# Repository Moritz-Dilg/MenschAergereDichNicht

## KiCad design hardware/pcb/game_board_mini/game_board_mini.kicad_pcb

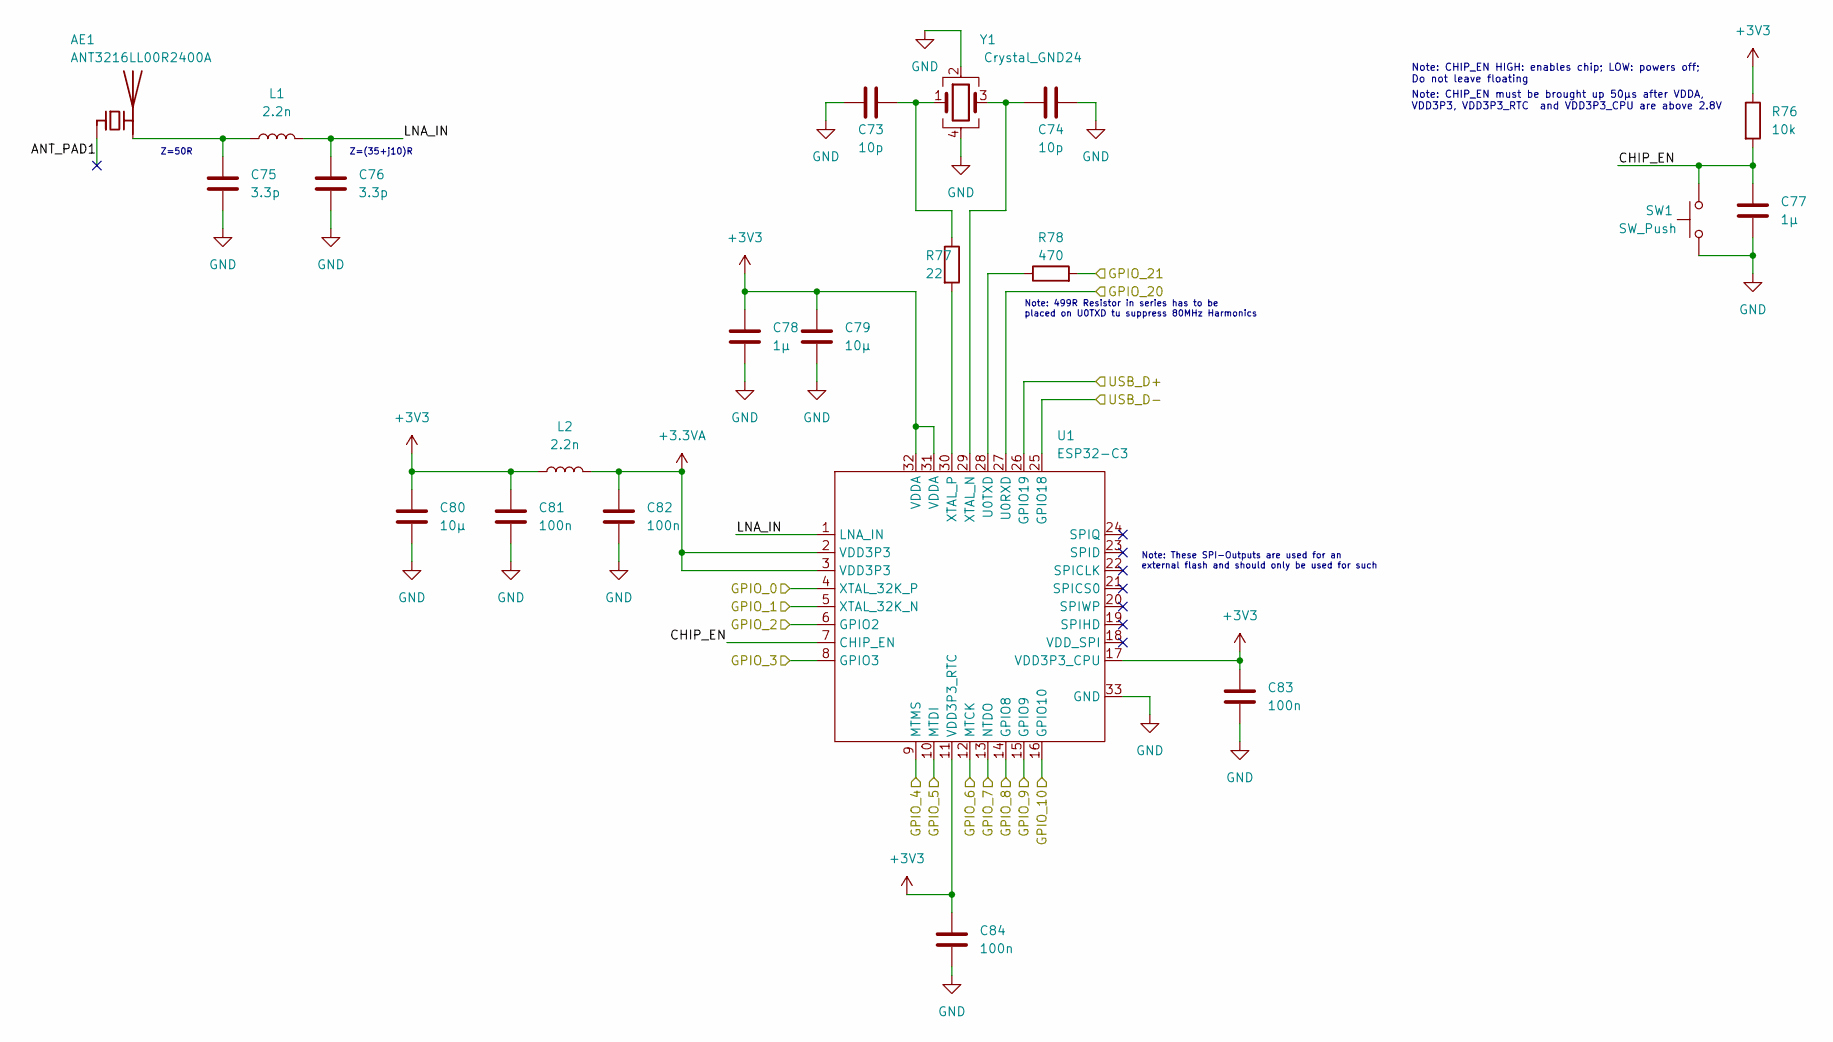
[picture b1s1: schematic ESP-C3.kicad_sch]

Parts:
AE1: ANT3216LL00R2400A
C73, C74: 10p; C_0603_1608Metric
C75, C76: 3.3p; C_0603_1608Metric
C77, C78: 1µ; C_0603_1608Metric
C79, C80: 10µ; C_0603_1608Metric
C81, C82, C83, C84: 100n; C_0603_1608Metric
L1, L2: 2.2n; L_0603_1608Metric
R76: 10k; R_0603_1608Metric
R77: 22; R_0603_1608Metric
R78: 470; R_0603_1608Metric
SW1: SW_Push
U1: ESP32-C3; QFN-32-1EP_5x5mm_P0.5mm_EP3.3x3.3mm_ThermalVias
Y1: Crystal_GND24; Crystal_SMD_3225-4Pin_3.2x2.5mm

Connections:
+3.3VA: C82.1, L2.2, U1.2 (VDD3P3), U1.3 (VDD3P3)
+3V3: C78.1, C79.1, C80.1, C81.1, C83.1, C84.1, L2.1, R76.1, U1.11 (VDD3P3_RTC), U1.17 (VDD3P3_CPU), U1.31 (VDDA), U1.32 (VDDA); also elsewhere on the board
/BL: U1.27 (U0RXD); also elsewhere on the board
/Button_1: U1.8 (GPIO3); also elsewhere on the board
/Button_2: U1.9 (MTMS); also elsewhere on the board
/Button_3: U1.10 (MTDI); also elsewhere on the board
/CS: U1.12 (MTCK); also elsewhere on the board
/Connectors/EN_TFT: R78.2
/DC: U1.13 (NTDO); also elsewhere on the board
/Din_BASE: U1.4 (XTAL_32K_P); also elsewhere on the board
/Din_FIELD: U1.5 (XTAL_32K_N); also elsewhere on the board
/Din_GOAL: U1.6 (GPIO2); also elsewhere on the board
/ESP-C3/ANT_PAD1: AE1.1 (FEED)
/ESP-C3/CHIP_EN: C77.1, R76.2, SW1.2, U1.7 (CHIP_EN)
/ESP-C3/LNA_IN: C76.1, L1.2, U1.1 (LNA_IN)
/ESP-C3/USB_D+: U1.26 (GPIO19); also elsewhere on the board
/ESP-C3/USB_D-: U1.25 (GPIO18); also elsewhere on the board
/MOSI: U1.16 (GPIO10); also elsewhere on the board
/RST: U1.14 (GPIO8); also elsewhere on the board
/SCK: U1.15 (GPIO9); also elsewhere on the board
GND: C73.1, C74.2, C75.2, C76.2, C77.2, C78.2, C79.2, C80.2, C81.2, C82.2, C83.2, C84.2, SW1.1, U1.33 (GND), Y1.2, Y1.4; also elsewhere on the board
unnamed: AE1.2 (PCB_Trace), C75.1, L1.1
unnamed: C73.2, R77.1, Y1.1
unnamed: C74.1, U1.29 (XTAL_N), Y1.3
unnamed: R77.2, U1.30 (XTAL_P)
unnamed: R78.1, U1.28 (U0TXD)

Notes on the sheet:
Note: 499R Resistor in series has to be placed on U0TXD tu suppress 80MHz Harmonics
Note: CHIP_EN must be brought up 50µs after VDDA, VDD3P3, VDD3P3_RTC and VDD3P3_CPU are above 2.8V
Note: CHIP_EN HIGH: enables chip; LOW: powers off; Do not leave floating
Z=50R
Note: These SPI-Outputs are used for an external flash and should only be used for such
Z=(35+j10)R

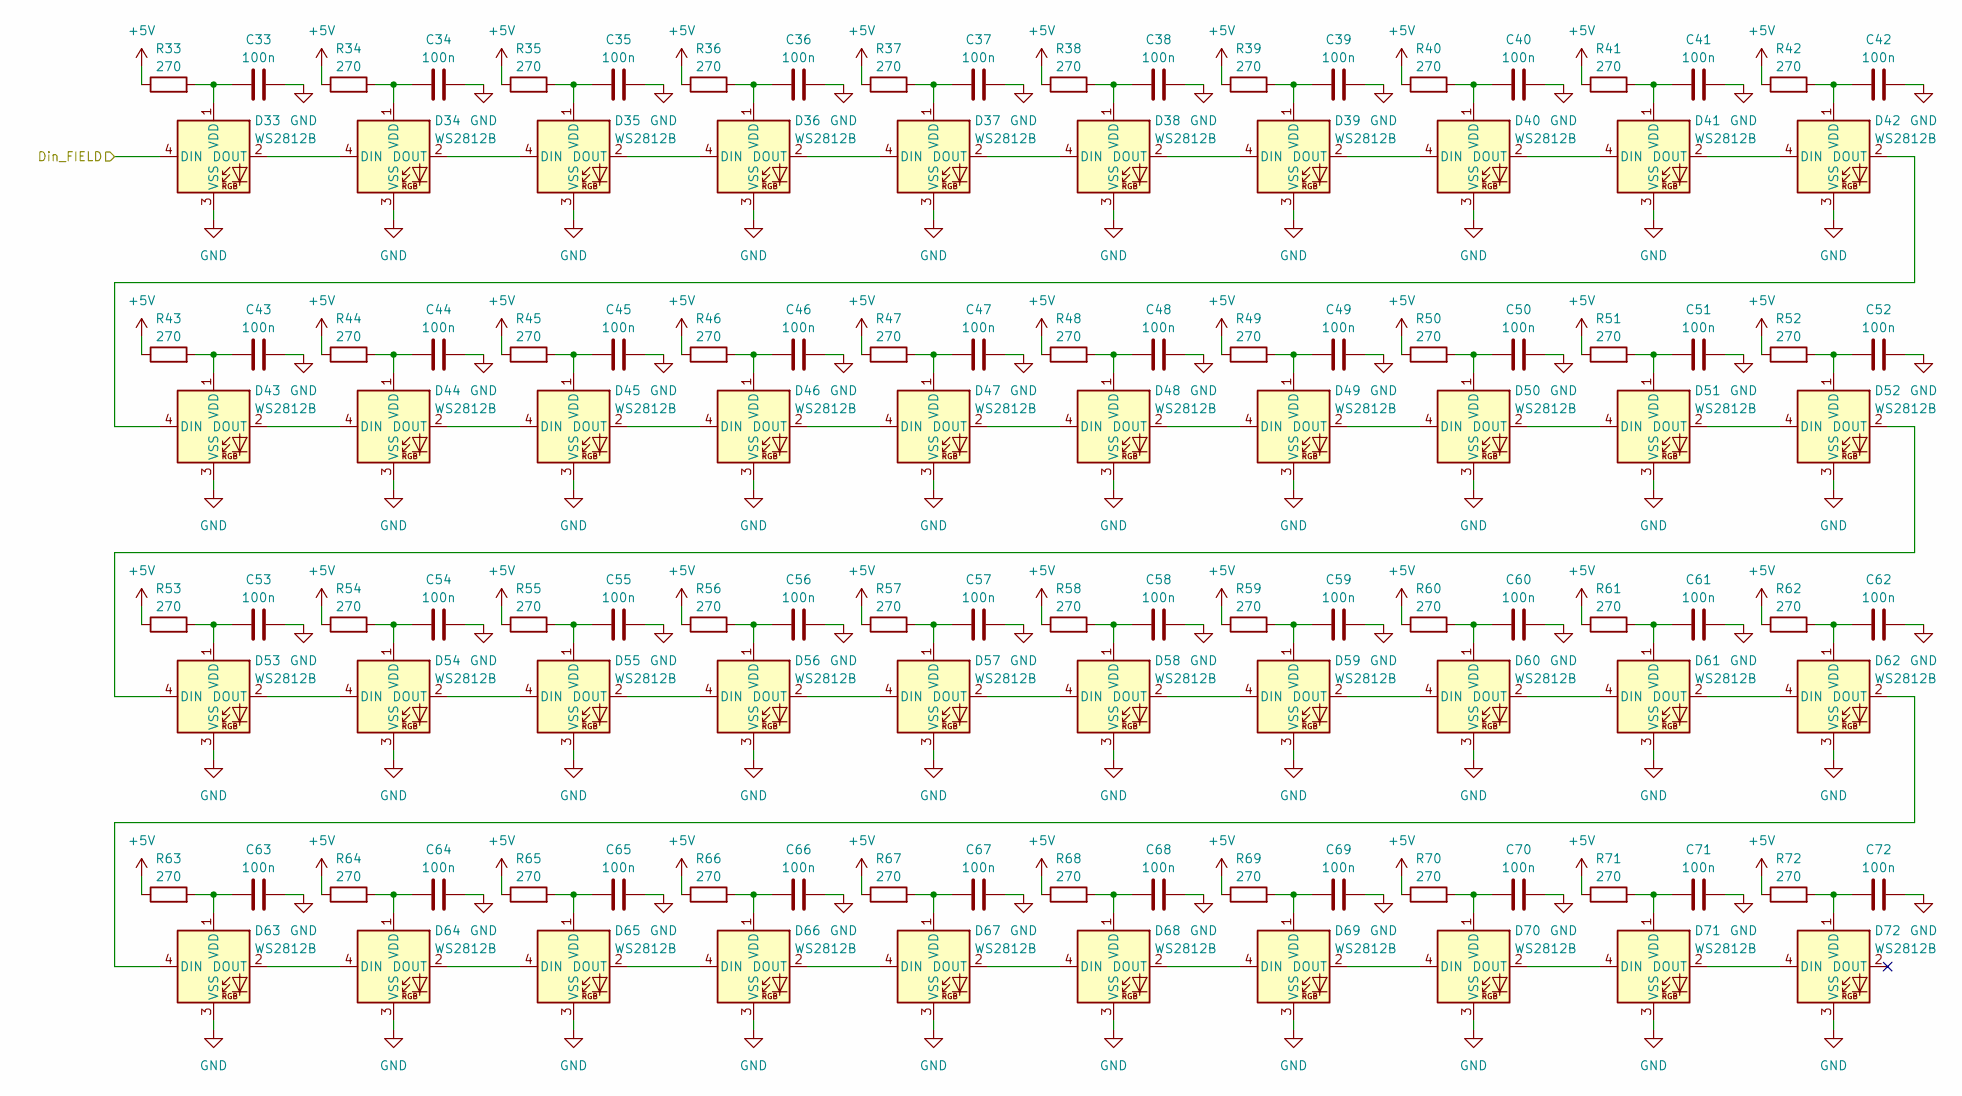
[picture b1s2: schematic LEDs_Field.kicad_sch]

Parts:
C33, C34, C35, C36, C37, C38, C39, C40, C41, C42, C43, C44, C45, C46, C47, C48, C49, C50, C51, C52, C53, C54, C55, C56, C57, C58, C59, C60, C61, C62, C63, C64, C65, C66, C67, C68, C69, C70, C71, C72: 100n; C_0603_1608Metric
D33, D34, D35, D36, D37, D38, D39, D40, D41, D42, D43, D44, D45, D46, D47, D48, D49, D50, D51, D52, D53, D54, D55, D56, D57, D58, D59, D60, D61, D62, D63, D64, D65, D66, D67, D68, D69, D70, D71, D72: WS2812B; LED_WS2812B-2020_PLCC4_2.0x2.0mm
R33, R34, R35, R36, R37, R38, R39, R40, R41, R42, R43, R44, R45, R46, R47, R48, R49, R50, R51, R52, R53, R54, R55, R56, R57, R58, R59, R60, R61, R62, R63, R64, R65, R66, R67, R68, R69, R70, R71, R72: 270; R_0603_1608Metric

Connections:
+5V: R33.1, R34.1, R35.1, R36.1, R37.1, R38.1, R39.1, R40.1, R41.1, R42.1, R43.1, R44.1, R45.1, R46.1, R47.1, R48.1, R49.1, R50.1, R51.1, R52.1, R53.1, R54.1, R55.1, R56.1, R57.1, R58.1, R59.1, R60.1, R61.1, R62.1, R63.1, R64.1, R65.1, R66.1, R67.1, R68.1, R69.1, R70.1, R71.1, R72.1; also elsewhere on the board
/Din_FIELD: D33.4 (DIN); also elsewhere on the board
GND: C33.2, C34.2, C35.2, C36.2, C37.2, C38.2, C39.2, C40.2, C41.2, C42.2, C43.2, C44.2, C45.2, C46.2, C47.2, C48.2, C49.2, C50.2, C51.2, C52.2, C53.2, C54.2, C55.2, C56.2, C57.2, C58.2, C59.2, C60.2, C61.2, C62.2, C63.2, C64.2, C65.2, C66.2, C67.2, C68.2, C69.2, C70.2, C71.2, C72.2, D33.3 (VSS), D34.3 (VSS), D35.3 (VSS), D36.3 (VSS), D37.3 (VSS), D38.3 (VSS), D39.3 (VSS), D40.3 (VSS), D41.3 (VSS), D42.3 (VSS), D43.3 (VSS), D44.3 (VSS), D45.3 (VSS), D46.3 (VSS), D47.3 (VSS), D48.3 (VSS), D49.3 (VSS), D50.3 (VSS), D51.3 (VSS), D52.3 (VSS), D53.3 (VSS), D54.3 (VSS), D55.3 (VSS), D56.3 (VSS), D57.3 (VSS), D58.3 (VSS), D59.3 (VSS), D60.3 (VSS), D61.3 (VSS), D62.3 (VSS), D63.3 (VSS), D64.3 (VSS), D65.3 (VSS), D66.3 (VSS), D67.3 (VSS), D68.3 (VSS), D69.3 (VSS), D70.3 (VSS), D71.3 (VSS), D72.3 (VSS); also elsewhere on the board
unnamed: C33.1, D33.1 (VDD), R33.2
unnamed: C34.1, D34.1 (VDD), R34.2
unnamed: C35.1, D35.1 (VDD), R35.2
unnamed: C36.1, D36.1 (VDD), R36.2
unnamed: C37.1, D37.1 (VDD), R37.2
unnamed: C38.1, D38.1 (VDD), R38.2
unnamed: C39.1, D39.1 (VDD), R39.2
unnamed: C40.1, D40.1 (VDD), R40.2
unnamed: C41.1, D41.1 (VDD), R41.2
unnamed: C42.1, D42.1 (VDD), R42.2
unnamed: C43.1, D43.1 (VDD), R43.2
unnamed: C44.1, D44.1 (VDD), R44.2
unnamed: C45.1, D45.1 (VDD), R45.2
unnamed: C46.1, D46.1 (VDD), R46.2
unnamed: C47.1, D47.1 (VDD), R47.2
unnamed: C48.1, D48.1 (VDD), R48.2
unnamed: C49.1, D49.1 (VDD), R49.2
unnamed: C50.1, D50.1 (VDD), R50.2
unnamed: C51.1, D51.1 (VDD), R51.2
unnamed: C52.1, D52.1 (VDD), R52.2
unnamed: C53.1, D53.1 (VDD), R53.2
unnamed: C54.1, D54.1 (VDD), R54.2
unnamed: C55.1, D55.1 (VDD), R55.2
unnamed: C56.1, D56.1 (VDD), R56.2
unnamed: C57.1, D57.1 (VDD), R57.2
unnamed: C58.1, D58.1 (VDD), R58.2
unnamed: C59.1, D59.1 (VDD), R59.2
unnamed: C60.1, D60.1 (VDD), R60.2
unnamed: C61.1, D61.1 (VDD), R61.2
unnamed: C62.1, D62.1 (VDD), R62.2
unnamed: C63.1, D63.1 (VDD), R63.2
unnamed: C64.1, D64.1 (VDD), R64.2
unnamed: C65.1, D65.1 (VDD), R65.2
unnamed: C66.1, D66.1 (VDD), R66.2
unnamed: C67.1, D67.1 (VDD), R67.2
unnamed: C68.1, D68.1 (VDD), R68.2
unnamed: C69.1, D69.1 (VDD), R69.2
unnamed: C70.1, D70.1 (VDD), R70.2
unnamed: C71.1, D71.1 (VDD), R71.2
unnamed: C72.1, D72.1 (VDD), R72.2
unnamed: D33.2 (DOUT), D34.4 (DIN)
unnamed: D34.2 (DOUT), D35.4 (DIN)
unnamed: D35.2 (DOUT), D36.4 (DIN)
unnamed: D36.2 (DOUT), D37.4 (DIN)
unnamed: D37.2 (DOUT), D38.4 (DIN)
unnamed: D38.2 (DOUT), D39.4 (DIN)
unnamed: D39.2 (DOUT), D40.4 (DIN)
unnamed: D40.2 (DOUT), D41.4 (DIN)
unnamed: D41.2 (DOUT), D42.4 (DIN)
unnamed: D42.2 (DOUT), D43.4 (DIN)
unnamed: D43.2 (DOUT), D44.4 (DIN)
unnamed: D44.2 (DOUT), D45.4 (DIN)
unnamed: D45.2 (DOUT), D46.4 (DIN)
unnamed: D46.2 (DOUT), D47.4 (DIN)
unnamed: D47.2 (DOUT), D48.4 (DIN)
unnamed: D48.2 (DOUT), D49.4 (DIN)
unnamed: D49.2 (DOUT), D50.4 (DIN)
unnamed: D50.2 (DOUT), D51.4 (DIN)
unnamed: D51.2 (DOUT), D52.4 (DIN)
unnamed: D52.2 (DOUT), D53.4 (DIN)
unnamed: D53.2 (DOUT), D54.4 (DIN)
unnamed: D54.2 (DOUT), D55.4 (DIN)
unnamed: D55.2 (DOUT), D56.4 (DIN)
unnamed: D56.2 (DOUT), D57.4 (DIN)
unnamed: D57.2 (DOUT), D58.4 (DIN)
unnamed: D58.2 (DOUT), D59.4 (DIN)
unnamed: D59.2 (DOUT), D60.4 (DIN)
unnamed: D60.2 (DOUT), D61.4 (DIN)
unnamed: D61.2 (DOUT), D62.4 (DIN)
unnamed: D62.2 (DOUT), D63.4 (DIN)
unnamed: D63.2 (DOUT), D64.4 (DIN)
unnamed: D64.2 (DOUT), D65.4 (DIN)
unnamed: D65.2 (DOUT), D66.4 (DIN)
unnamed: D66.2 (DOUT), D67.4 (DIN)
unnamed: D67.2 (DOUT), D68.4 (DIN)
unnamed: D68.2 (DOUT), D69.4 (DIN)
unnamed: D69.2 (DOUT), D70.4 (DIN)
unnamed: D70.2 (DOUT), D71.4 (DIN)
unnamed: D71.2 (DOUT), D72.4 (DIN)

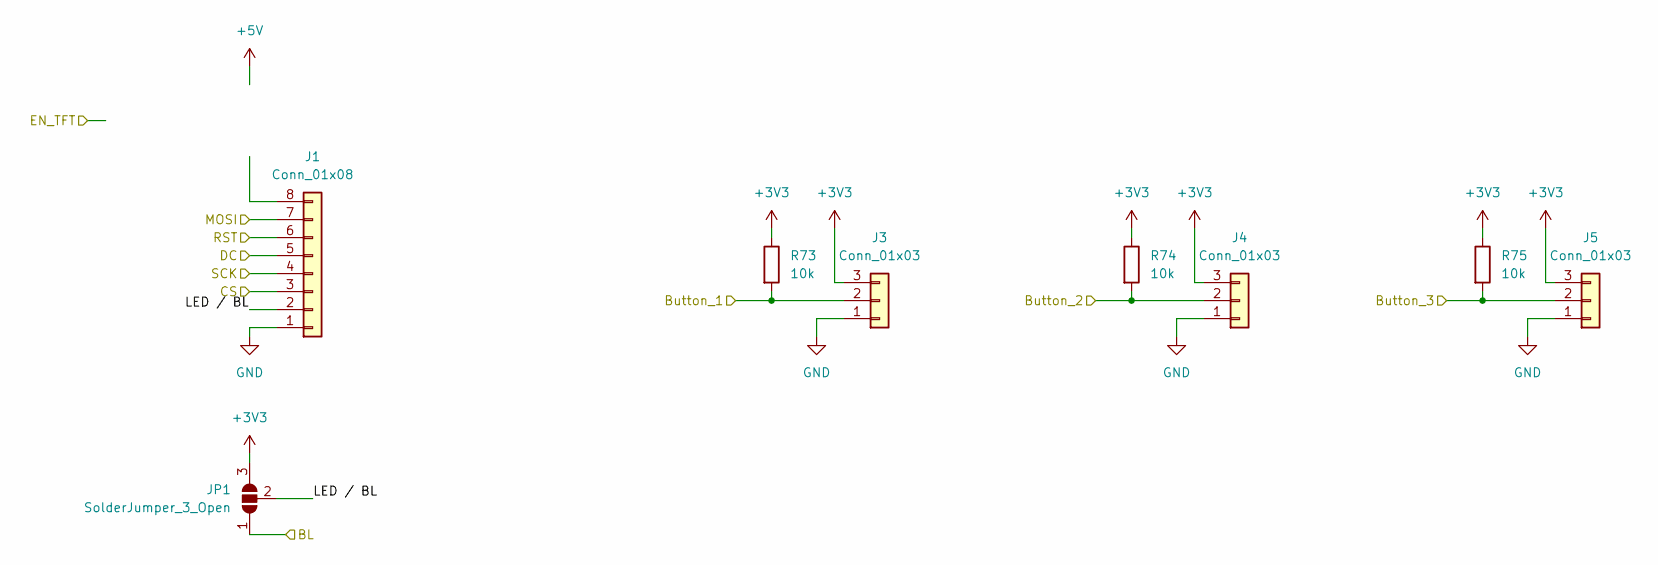
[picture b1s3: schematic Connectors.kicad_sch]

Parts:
J1: Conn_01x08; JST_PH_B8B-PH-K_1x08_P2.00mm_Vertical
J3, J4, J5: Conn_01x03; JST_PH_B3B-PH-K_1x03_P2.00mm_Vertical
JP1: SolderJumper_3_Open; SolderJumper-3_P1.3mm_Open_Pad1.0x1.5mm
R73, R74, R75: 10k; R_0805_2012Metric

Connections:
+3V3: J3.3, J4.3, J5.3, JP1.3 (B), R73.1, R74.1, R75.1; also elsewhere on the board
/BL: JP1.1 (A); also elsewhere on the board
/Button_1: J3.2, R73.2; also elsewhere on the board
/Button_2: J4.2, R74.2; also elsewhere on the board
/Button_3: J5.2, R75.2; also elsewhere on the board
/CS: J1.3; also elsewhere on the board
/Connectors/LED / BL: J1.2, JP1.2 (C)
/DC: J1.5; also elsewhere on the board
/MOSI: J1.7; also elsewhere on the board
/RST: J1.6; also elsewhere on the board
/SCK: J1.4; also elsewhere on the board
GND: J1.1, J3.1, J4.1, J5.1; also elsewhere on the board

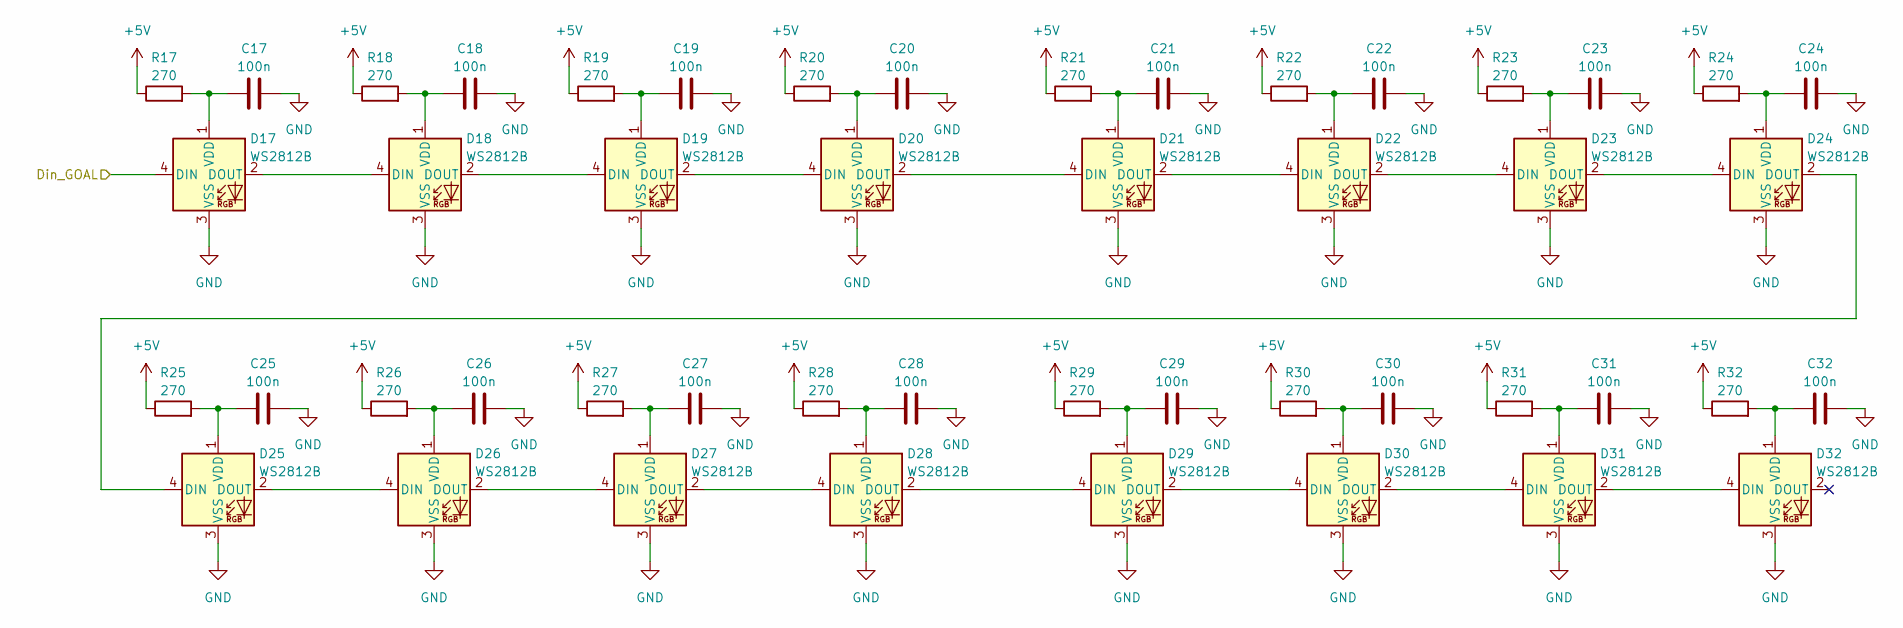
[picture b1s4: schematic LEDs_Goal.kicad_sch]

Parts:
C17, C18, C19, C20, C21, C22, C23, C24, C25, C26, C27, C28, C29, C30, C31, C32: 100n; C_0603_1608Metric
D17, D18, D19, D20, D21, D22, D23, D24, D25, D26, D27, D28, D29, D30, D31, D32: WS2812B; LED_WS2812B-2020_PLCC4_2.0x2.0mm
R17, R18, R19, R20, R21, R22, R23, R24, R25, R26, R27, R28, R29, R30, R31, R32: 270; R_0603_1608Metric

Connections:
+5V: R17.1, R18.1, R19.1, R20.1, R21.1, R22.1, R23.1, R24.1, R25.1, R26.1, R27.1, R28.1, R29.1, R30.1, R31.1, R32.1; also elsewhere on the board
/Din_GOAL: D17.4 (DIN); also elsewhere on the board
GND: C17.2, C18.2, C19.2, C20.2, C21.2, C22.2, C23.2, C24.2, C25.2, C26.2, C27.2, C28.2, C29.2, C30.2, C31.2, C32.2, D17.3 (VSS), D18.3 (VSS), D19.3 (VSS), D20.3 (VSS), D21.3 (VSS), D22.3 (VSS), D23.3 (VSS), D24.3 (VSS), D25.3 (VSS), D26.3 (VSS), D27.3 (VSS), D28.3 (VSS), D29.3 (VSS), D30.3 (VSS), D31.3 (VSS), D32.3 (VSS); also elsewhere on the board
unnamed: C17.1, D17.1 (VDD), R17.2
unnamed: C18.1, D18.1 (VDD), R18.2
unnamed: C19.1, D19.1 (VDD), R19.2
unnamed: C20.1, D20.1 (VDD), R20.2
unnamed: C21.1, D21.1 (VDD), R21.2
unnamed: C22.1, D22.1 (VDD), R22.2
unnamed: C23.1, D23.1 (VDD), R23.2
unnamed: C24.1, D24.1 (VDD), R24.2
unnamed: C25.1, D25.1 (VDD), R25.2
unnamed: C26.1, D26.1 (VDD), R26.2
unnamed: C27.1, D27.1 (VDD), R27.2
unnamed: C28.1, D28.1 (VDD), R28.2
unnamed: C29.1, D29.1 (VDD), R29.2
unnamed: C30.1, D30.1 (VDD), R30.2
unnamed: C31.1, D31.1 (VDD), R31.2
unnamed: C32.1, D32.1 (VDD), R32.2
unnamed: D17.2 (DOUT), D18.4 (DIN)
unnamed: D18.2 (DOUT), D19.4 (DIN)
unnamed: D19.2 (DOUT), D20.4 (DIN)
unnamed: D20.2 (DOUT), D21.4 (DIN)
unnamed: D21.2 (DOUT), D22.4 (DIN)
unnamed: D22.2 (DOUT), D23.4 (DIN)
unnamed: D23.2 (DOUT), D24.4 (DIN)
unnamed: D24.2 (DOUT), D25.4 (DIN)
unnamed: D25.2 (DOUT), D26.4 (DIN)
unnamed: D26.2 (DOUT), D27.4 (DIN)
unnamed: D27.2 (DOUT), D28.4 (DIN)
unnamed: D28.2 (DOUT), D29.4 (DIN)
unnamed: D29.2 (DOUT), D30.4 (DIN)
unnamed: D30.2 (DOUT), D31.4 (DIN)
unnamed: D31.2 (DOUT), D32.4 (DIN)

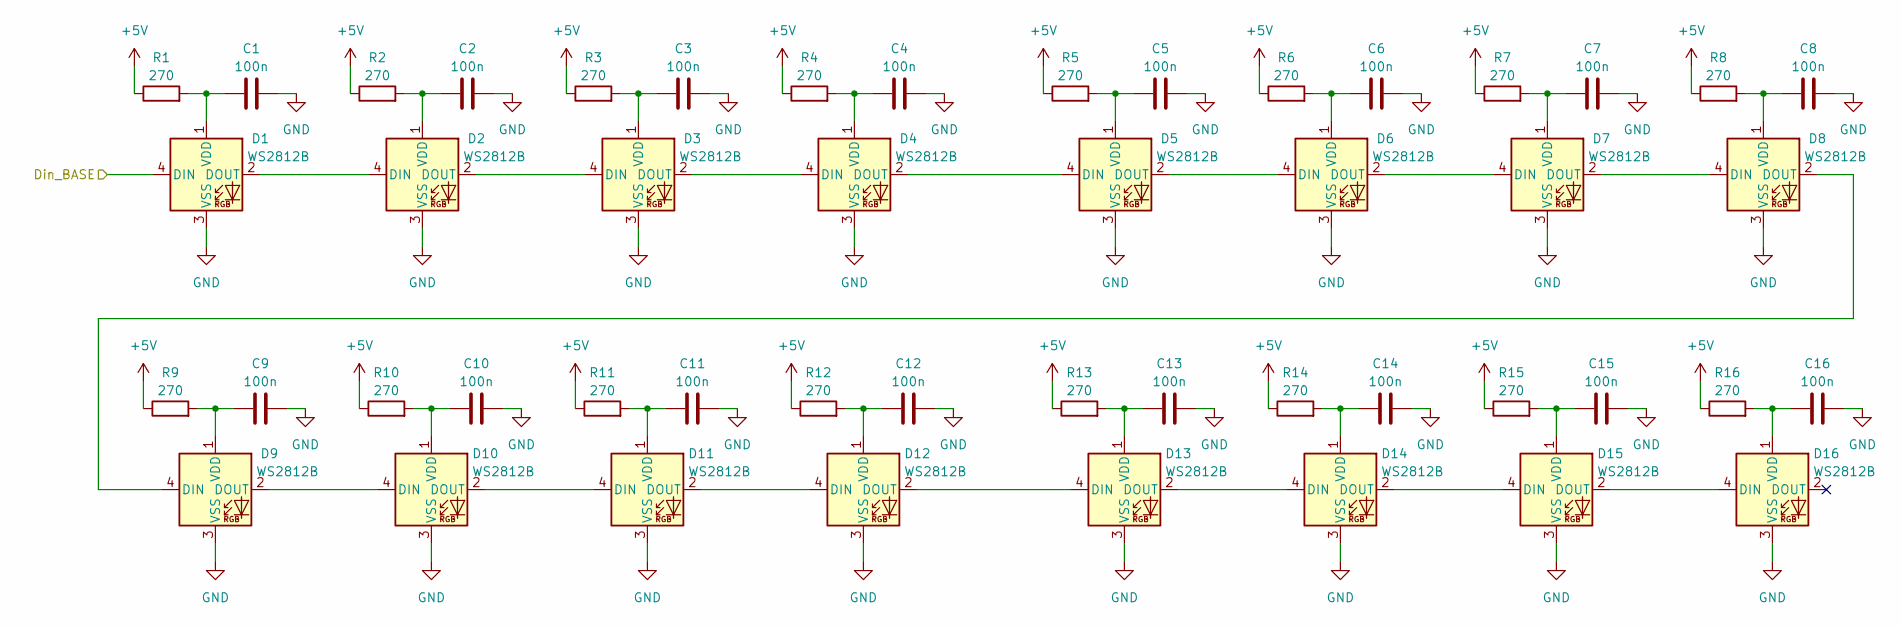
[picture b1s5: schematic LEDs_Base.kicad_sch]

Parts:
C1, C2, C3, C4, C5, C6, C7, C8, C9, C10, C11, C12, C13, C14, C15, C16: 100n; C_0603_1608Metric
D1, D2, D3, D4, D5, D6, D7, D8, D9, D10, D11, D12, D13, D14, D15, D16: WS2812B; LED_WS2812B-2020_PLCC4_2.0x2.0mm
R1, R2, R3, R4, R5, R6, R7, R8, R9, R10, R11, R12, R13, R14, R15, R16: 270; R_0603_1608Metric

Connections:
+5V: R1.1, R2.1, R3.1, R4.1, R5.1, R6.1, R7.1, R8.1, R9.1, R10.1, R11.1, R12.1, R13.1, R14.1, R15.1, R16.1; also elsewhere on the board
/Din_BASE: D1.4 (DIN); also elsewhere on the board
GND: C1.2, C2.2, C3.2, C4.2, C5.2, C6.2, C7.2, C8.2, C9.2, C10.2, C11.2, C12.2, C13.2, C14.2, C15.2, C16.2, D1.3 (VSS), D2.3 (VSS), D3.3 (VSS), D4.3 (VSS), D5.3 (VSS), D6.3 (VSS), D7.3 (VSS), D8.3 (VSS), D9.3 (VSS), D10.3 (VSS), D11.3 (VSS), D12.3 (VSS), D13.3 (VSS), D14.3 (VSS), D15.3 (VSS), D16.3 (VSS); also elsewhere on the board
unnamed: C1.1, D1.1 (VDD), R1.2
unnamed: C2.1, D2.1 (VDD), R2.2
unnamed: C3.1, D3.1 (VDD), R3.2
unnamed: C4.1, D4.1 (VDD), R4.2
unnamed: C5.1, D5.1 (VDD), R5.2
unnamed: C6.1, D6.1 (VDD), R6.2
unnamed: C7.1, D7.1 (VDD), R7.2
unnamed: C8.1, D8.1 (VDD), R8.2
unnamed: C9.1, D9.1 (VDD), R9.2
unnamed: C10.1, D10.1 (VDD), R10.2
unnamed: C11.1, D11.1 (VDD), R11.2
unnamed: C12.1, D12.1 (VDD), R12.2
unnamed: C13.1, D13.1 (VDD), R13.2
unnamed: C14.1, D14.1 (VDD), R14.2
unnamed: C15.1, D15.1 (VDD), R15.2
unnamed: C16.1, D16.1 (VDD), R16.2
unnamed: D1.2 (DOUT), D2.4 (DIN)
unnamed: D2.2 (DOUT), D3.4 (DIN)
unnamed: D3.2 (DOUT), D4.4 (DIN)
unnamed: D4.2 (DOUT), D5.4 (DIN)
unnamed: D5.2 (DOUT), D6.4 (DIN)
unnamed: D6.2 (DOUT), D7.4 (DIN)
unnamed: D7.2 (DOUT), D8.4 (DIN)
unnamed: D8.2 (DOUT), D9.4 (DIN)
unnamed: D10.2 (DOUT), D11.4 (DIN)
unnamed: D9.2 (DOUT), D10.4 (DIN)
unnamed: D11.2 (DOUT), D12.4 (DIN)
unnamed: D12.2 (DOUT), D13.4 (DIN)
unnamed: D13.2 (DOUT), D14.4 (DIN)
unnamed: D14.2 (DOUT), D15.4 (DIN)
unnamed: D15.2 (DOUT), D16.4 (DIN)

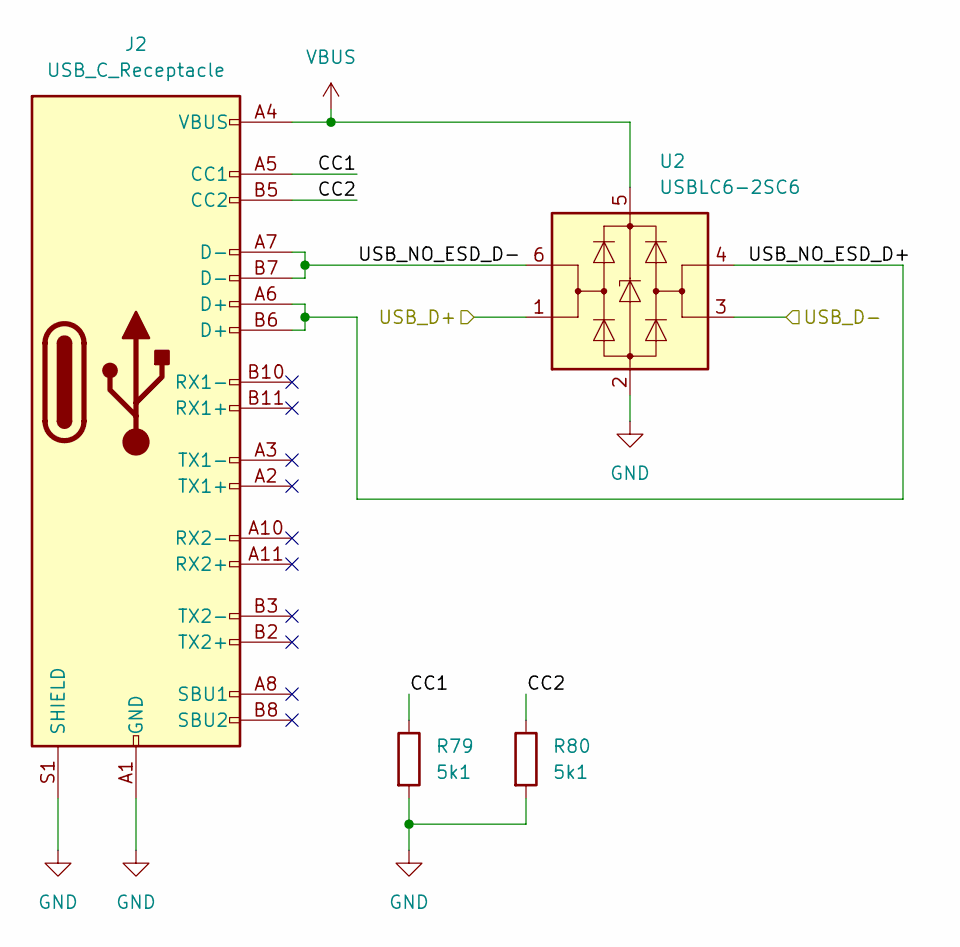
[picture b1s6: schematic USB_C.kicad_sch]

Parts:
J2: USB_C_Receptacle; USB_C_MOLEX_1054500101
R79, R80: 5k1; R_0603_1608Metric
U2: USBLC6-2SC6; SOT-23-6

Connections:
/ESP-C3/USB_D+: U2.1 (I/O1); also elsewhere on the board
/ESP-C3/USB_D-: U2.3 (I/O2); also elsewhere on the board
/USB_C/CC1: J2.A5 (CC1), R79.1
/USB_C/CC2: J2.B5 (CC2), R80.1
/USB_C/USB_NO_ESD_D+: J2.A6 (D+), J2.B6 (D+), U2.4 (I/O2)
/USB_C/USB_NO_ESD_D-: J2.A7 (D-), J2.B7 (D-), U2.6 (I/O1)
GND: J2.A1 (GND), J2.A12 (GND), J2.B1 (GND), J2.B12 (GND), J2.S1 (SHIELD), R79.2, R80.2, U2.2 (GND); also elsewhere on the board
VBUS: J2.A4 (VBUS), J2.A9 (VBUS), J2.B4 (VBUS), J2.B9 (VBUS), U2.5 (VBUS)

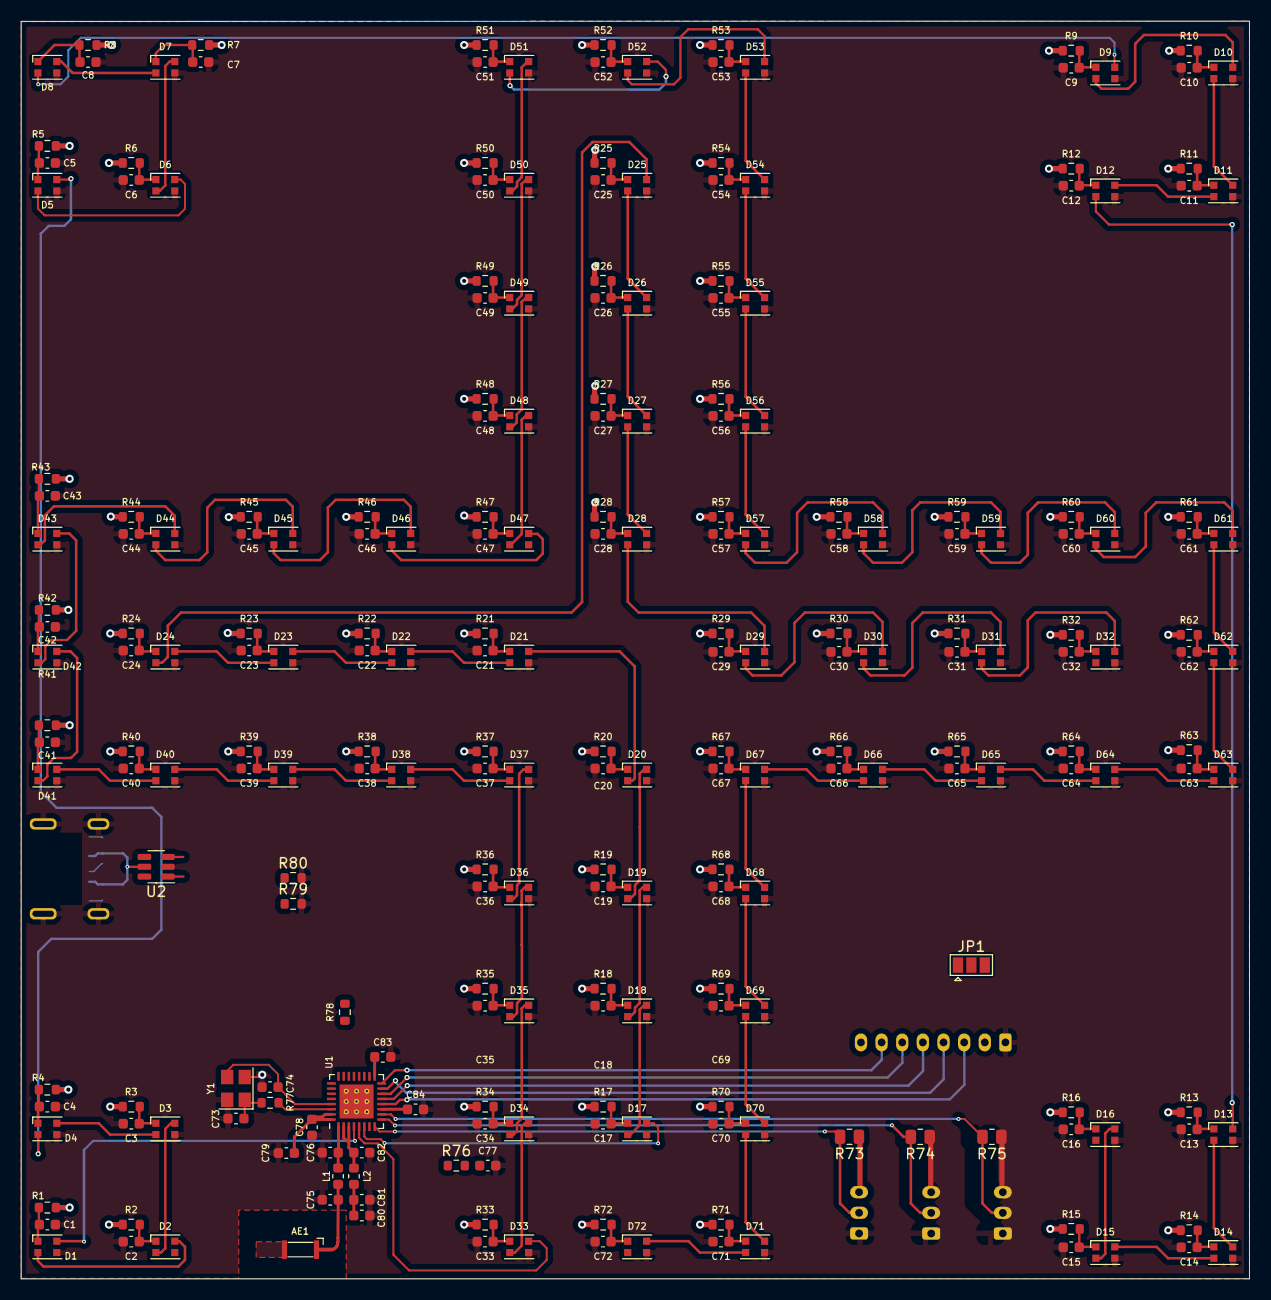
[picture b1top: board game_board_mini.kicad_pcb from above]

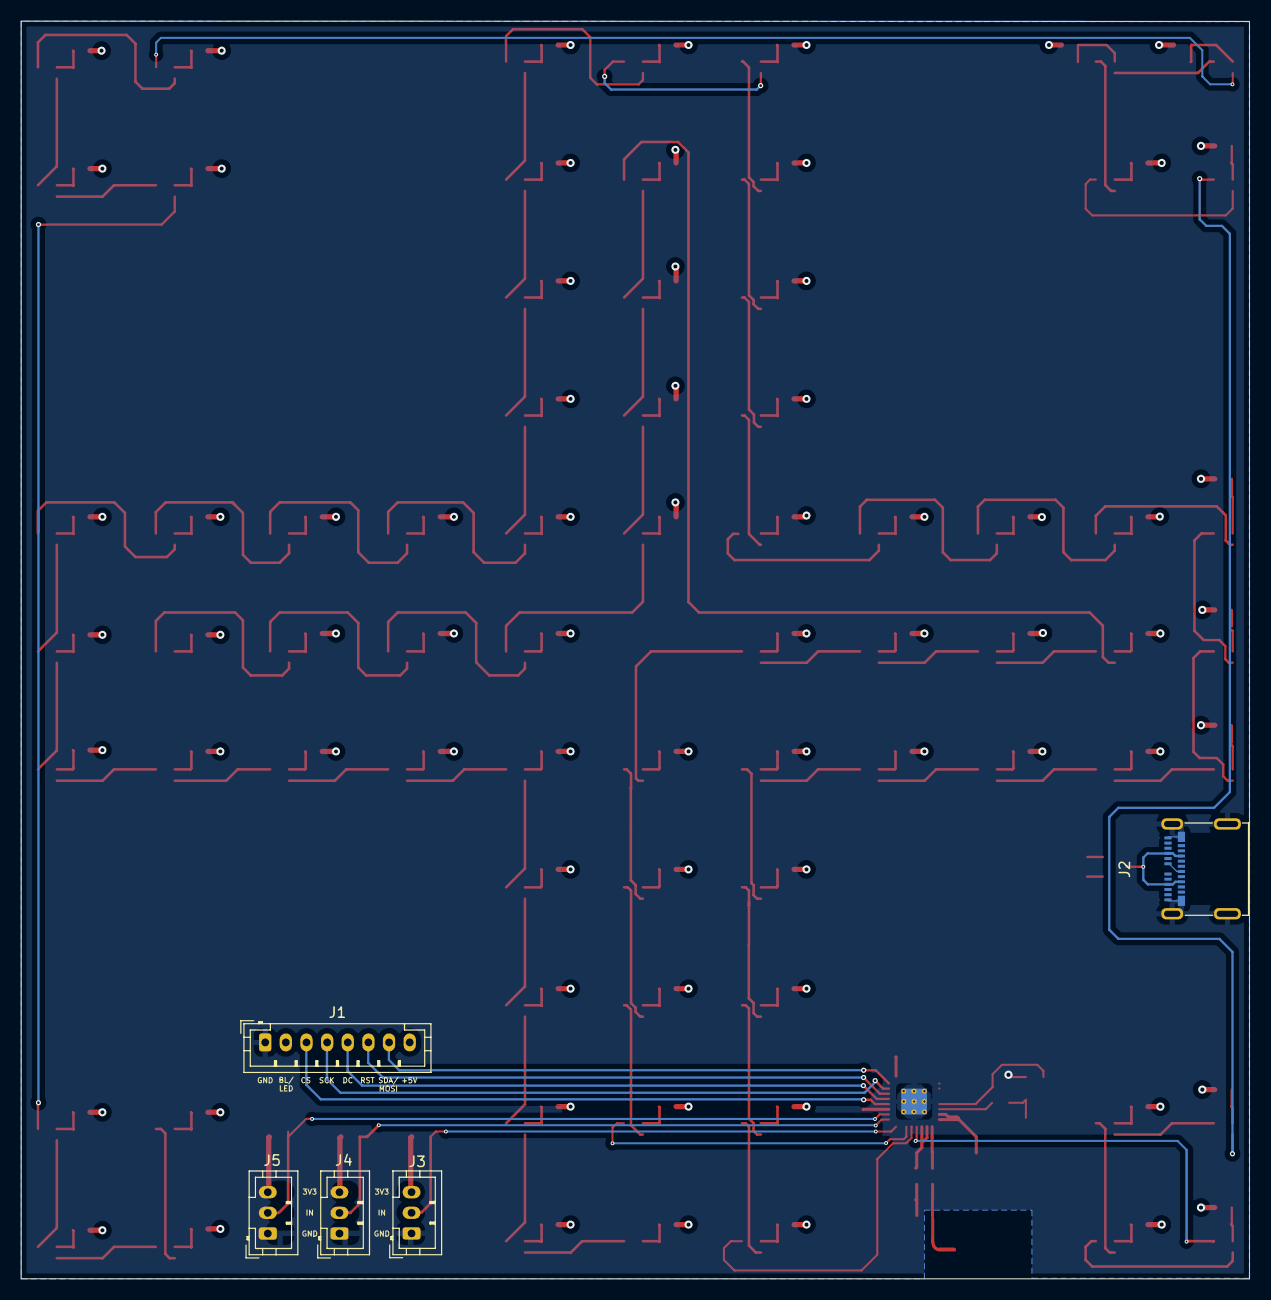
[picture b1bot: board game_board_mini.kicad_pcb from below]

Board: 2 copper layers, 119.0 x 121.9 mm, 248 parts (5 on the bottom side), 172 nets.

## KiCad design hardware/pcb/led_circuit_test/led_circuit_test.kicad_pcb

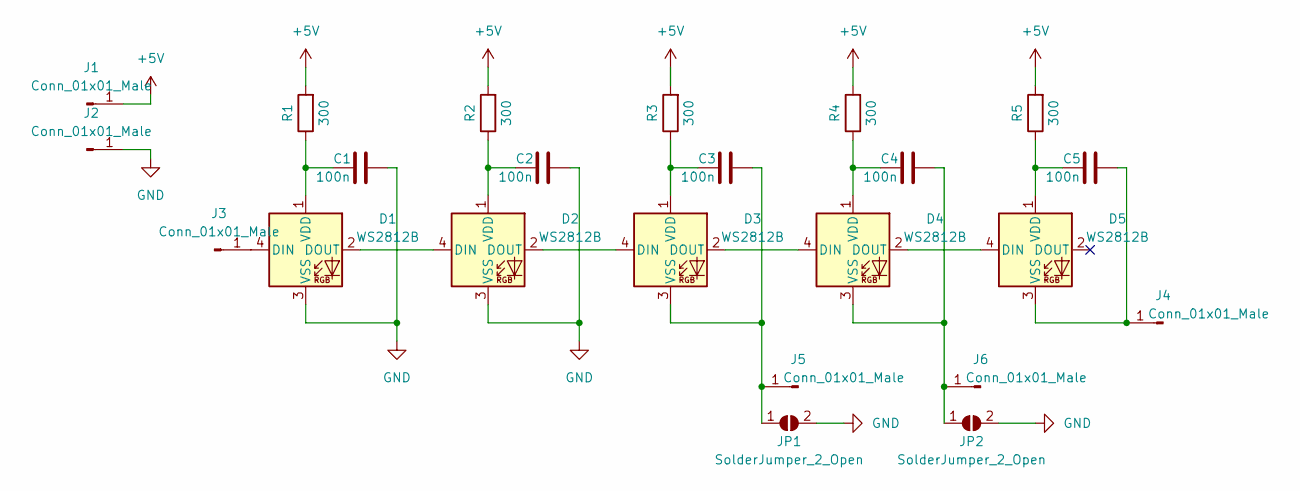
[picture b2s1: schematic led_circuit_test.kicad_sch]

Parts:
C1, C2, C3, C4, C5: 100n; C_0805_2012Metric
D1, D2, D3, D4, D5: WS2812B; LED_WS2812B_PLCC4_5.0x5.0mm_P3.2mm
J1, J2, J3, J4, J5, J6: Conn_01x01_Male; TestPoint_Pad_3.0x3.0mm
JP1, JP2: SolderJumper_2_Open; SolderJumper-2_P1.3mm_Open_RoundedPad1.0x1.5mm
R1, R2, R3, R4, R5: 300; R_0805_2012Metric

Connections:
+5V: J1.1, R1.2, R2.2, R3.2, R4.2, R5.2
GND: C1.2, C2.2, D1.3 (VSS), D2.3 (VSS), J2.1, JP1.2 (B), JP2.2 (B)
unnamed: C1.1, D1.1 (VDD), R1.1
unnamed: C2.1, D2.1 (VDD), R2.1
unnamed: C3.1, D3.1 (VDD), R3.1
unnamed: C3.2, D3.3 (VSS), J5.1, JP1.1 (A)
unnamed: C4.1, D4.1 (VDD), R4.1
unnamed: C4.2, D4.3 (VSS), J6.1, JP2.1 (A)
unnamed: C5.1, D5.1 (VDD), R5.1
unnamed: C5.2, D5.3 (VSS), J4.1
unnamed: D1.2 (DOUT), D2.4 (DIN)
unnamed: D1.4 (DIN), J3.1
unnamed: D2.2 (DOUT), D3.4 (DIN)
unnamed: D3.2 (DOUT), D4.4 (DIN)
unnamed: D4.2 (DOUT), D5.4 (DIN)

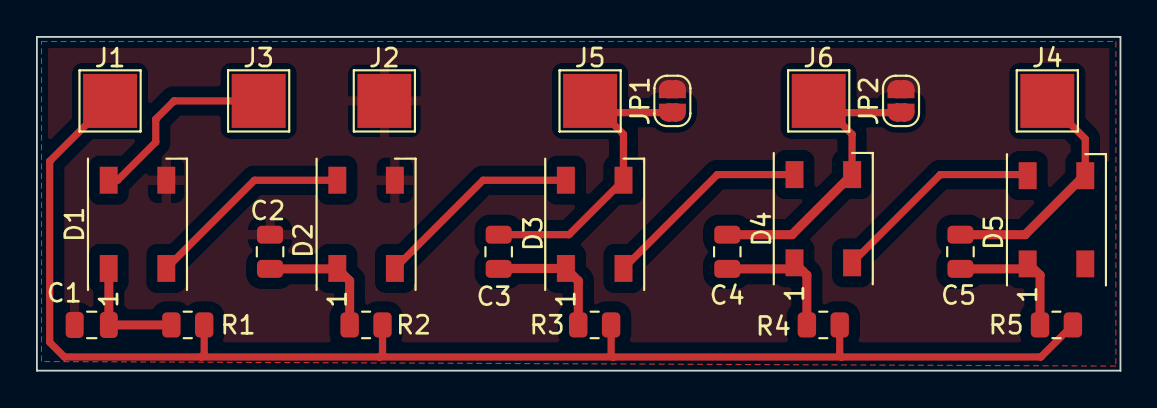
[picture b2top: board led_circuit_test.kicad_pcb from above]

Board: 2 copper layers, 60.2 x 18.5 mm, 23 parts (0 on the bottom side), 15 nets.

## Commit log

2022-09-30 Added LICENSE
2022-09-30 Added datasheets
2022-10-03 LED function for base
2022-10-03 LED function for goal
2022-10-03 LED function for field
2022-10-03 Added type header
2022-10-03 Updated naming
2022-10-03 Combined LED.begin() and LED constructor
2022-10-03 Fixed error: unable to init LED
2022-10-03 Add Figure structure
2022-10-03 Fixed error: goal LEDs
2022-10-03 Added LED functions to set and remove Figures
2022-10-04 Implemented Figure functions; TODO: select(), deselect(), Check if pos. in Goal is free
2022-10-14 Updated javadoc
2022-10-14 Add Game and Player headers
2022-10-14 Change references to pointers
2022-10-14 add Game.cpp & update headers
2022-10-16 Designed small PCB to test LED circuit and LED control
2022-10-21 Remove selection code, add position getters
2022-10-21 Add figure selector structure
2022-10-21 add player implementation
2022-10-21 figure selection code & javadoc fix
2022-10-21 update types (belongs to previous commit)
2022-10-23 Updated and enhanced test PCB after testing
2022-11-02 Basic display control (with Nextion and standard TFT)
2022-11-11 Add ISR for btn press
2022-11-13 Drew PCB - TODO: Button connections
2022-11-18 Finished PCB
2022-11-18 Implement figure capturing
2022-11-18 PCB: Generated gerber & images
2022-11-20 Removed `Nextion` directory + sample code (not needed)
2022-11-20 Fixed bug: Figure position was updated too early
2022-11-25 Added GFX for display control to Game and Player
2022-12-05 Fixed compilation errors - TODO: Fix Buttons
2022-12-20 First set of bugfixes
2023-01-27 Updated color of yellow
2023-01-28 Started with schematic for small board with ESP32-C3 SOC
2023-02-01 [PCB] Finished ESP Schematic
2023-02-01 Added missing datasheets
2023-02-03 Set & Clear Figure for toggling
2023-02-03 [PCB] Started routing (LEDs almost done, ESP started)
2023-02-03 Added missing datasheet of USB-C connector
2023-02-04 [PCB] Routed ESP
2023-02-06 [PCB] Increased board size
2023-02-10 Added FigureSelector
2023-02-13 Fixed leds not blinking in goal
2023-02-14 Fixed 6s being discarded by the game & implemented rule for moving figures at start
2023-02-14 Renamed buttons from 1, 2, 3 to A, B, C
2023-02-15 Added TFT Library
2023-02-15 Fixed incorrect button naming
2023-02-15 Updated Game with TFT Library
2023-02-15 Fixed current player not displaying correctly
2023-02-16 Deleted unused file
2023-02-17 First clear button, then set
2023-02-17 Added correct button description
2023-02-17 Add player count
2023-02-17 Added custom Button library and starting-selector
2023-02-17 Set TFT to balck after exiting
2023-02-17 Fixed bug: clearing goal path on new entry
2023-02-17 Bugfixes
2023-03-10 Added winning to the game
2023-03-10 Added functions to set text manually
2023-03-10 Clear whole board
2023-03-10 esp deep sleep on exit
2023-03-10 Clear dice result on new player
2023-03-17 Removed unnessecary variable
2023-03-17 Clear LEDs on startup and on shutdown
2023-03-17 Settings screen
2023-03-18 (hopefully) Fixed bug: Butotn text not always displaying
2023-03-18 Display player who won
2023-03-18 Clear all LEDs on new game
2023-03-18 Clear screen after settings
2023-03-18 Removed redundand TODO
2023-03-19 Display correct coler when won (did not match if player_count == 2)
2023-03-20 Change player count && LED brightness (NOT TESTED!)
2023-03-20 Removed unnessecary TODOs
2023-03-20 Removed unnessecary define
2023-03-22 Fixed wrong function declaration
2023-03-22 Fix figure moving with none in base
2023-03-23 Only roll dice 3 times if cannot move any figure (goal!!) NOT TESTED
2023-03-24 Update TFT at change of setting
2023-03-24 Fixed bug: `player_count` and `brightness` reset in loop
2023-03-24 Preview brightness in settings
2023-03-24 Fixed bug: set correct button assignment on tft for settings
2023-03-24 Only roll dice 3 times if cannot move any figure (goal!!) NOT TESTED v2
2023-03-26 Fix only having only 2 tries to roll instead of 3
2023-03-28 Field background (always show LEDs for better visibility)
2023-03-29 Fixed bug: wrong RGB val for clearing LED in Yellow Goal
2023-03-29 Quick implementation of quit game
2023-03-29 Fixed bug: Figureselector called twice
2023-03-29 Added delay after three times rolling dice and not succeeding
2023-03-29 Updated Button allocation
2023-03-29 Fixed bug: only showing number of bases needed in `initField` (`player_count`)
2023-03-30 Only roll dice 3 times if cannot move any figure (goal!!) NOT TESTED v3
2023-03-31 Only roll dice 3 times if cannot move any figure (goal!!) v4
2023-03-31 Updated Delay after turn of each player
2023-04-06 [PCB] Current board
2023-04-17 sockets
